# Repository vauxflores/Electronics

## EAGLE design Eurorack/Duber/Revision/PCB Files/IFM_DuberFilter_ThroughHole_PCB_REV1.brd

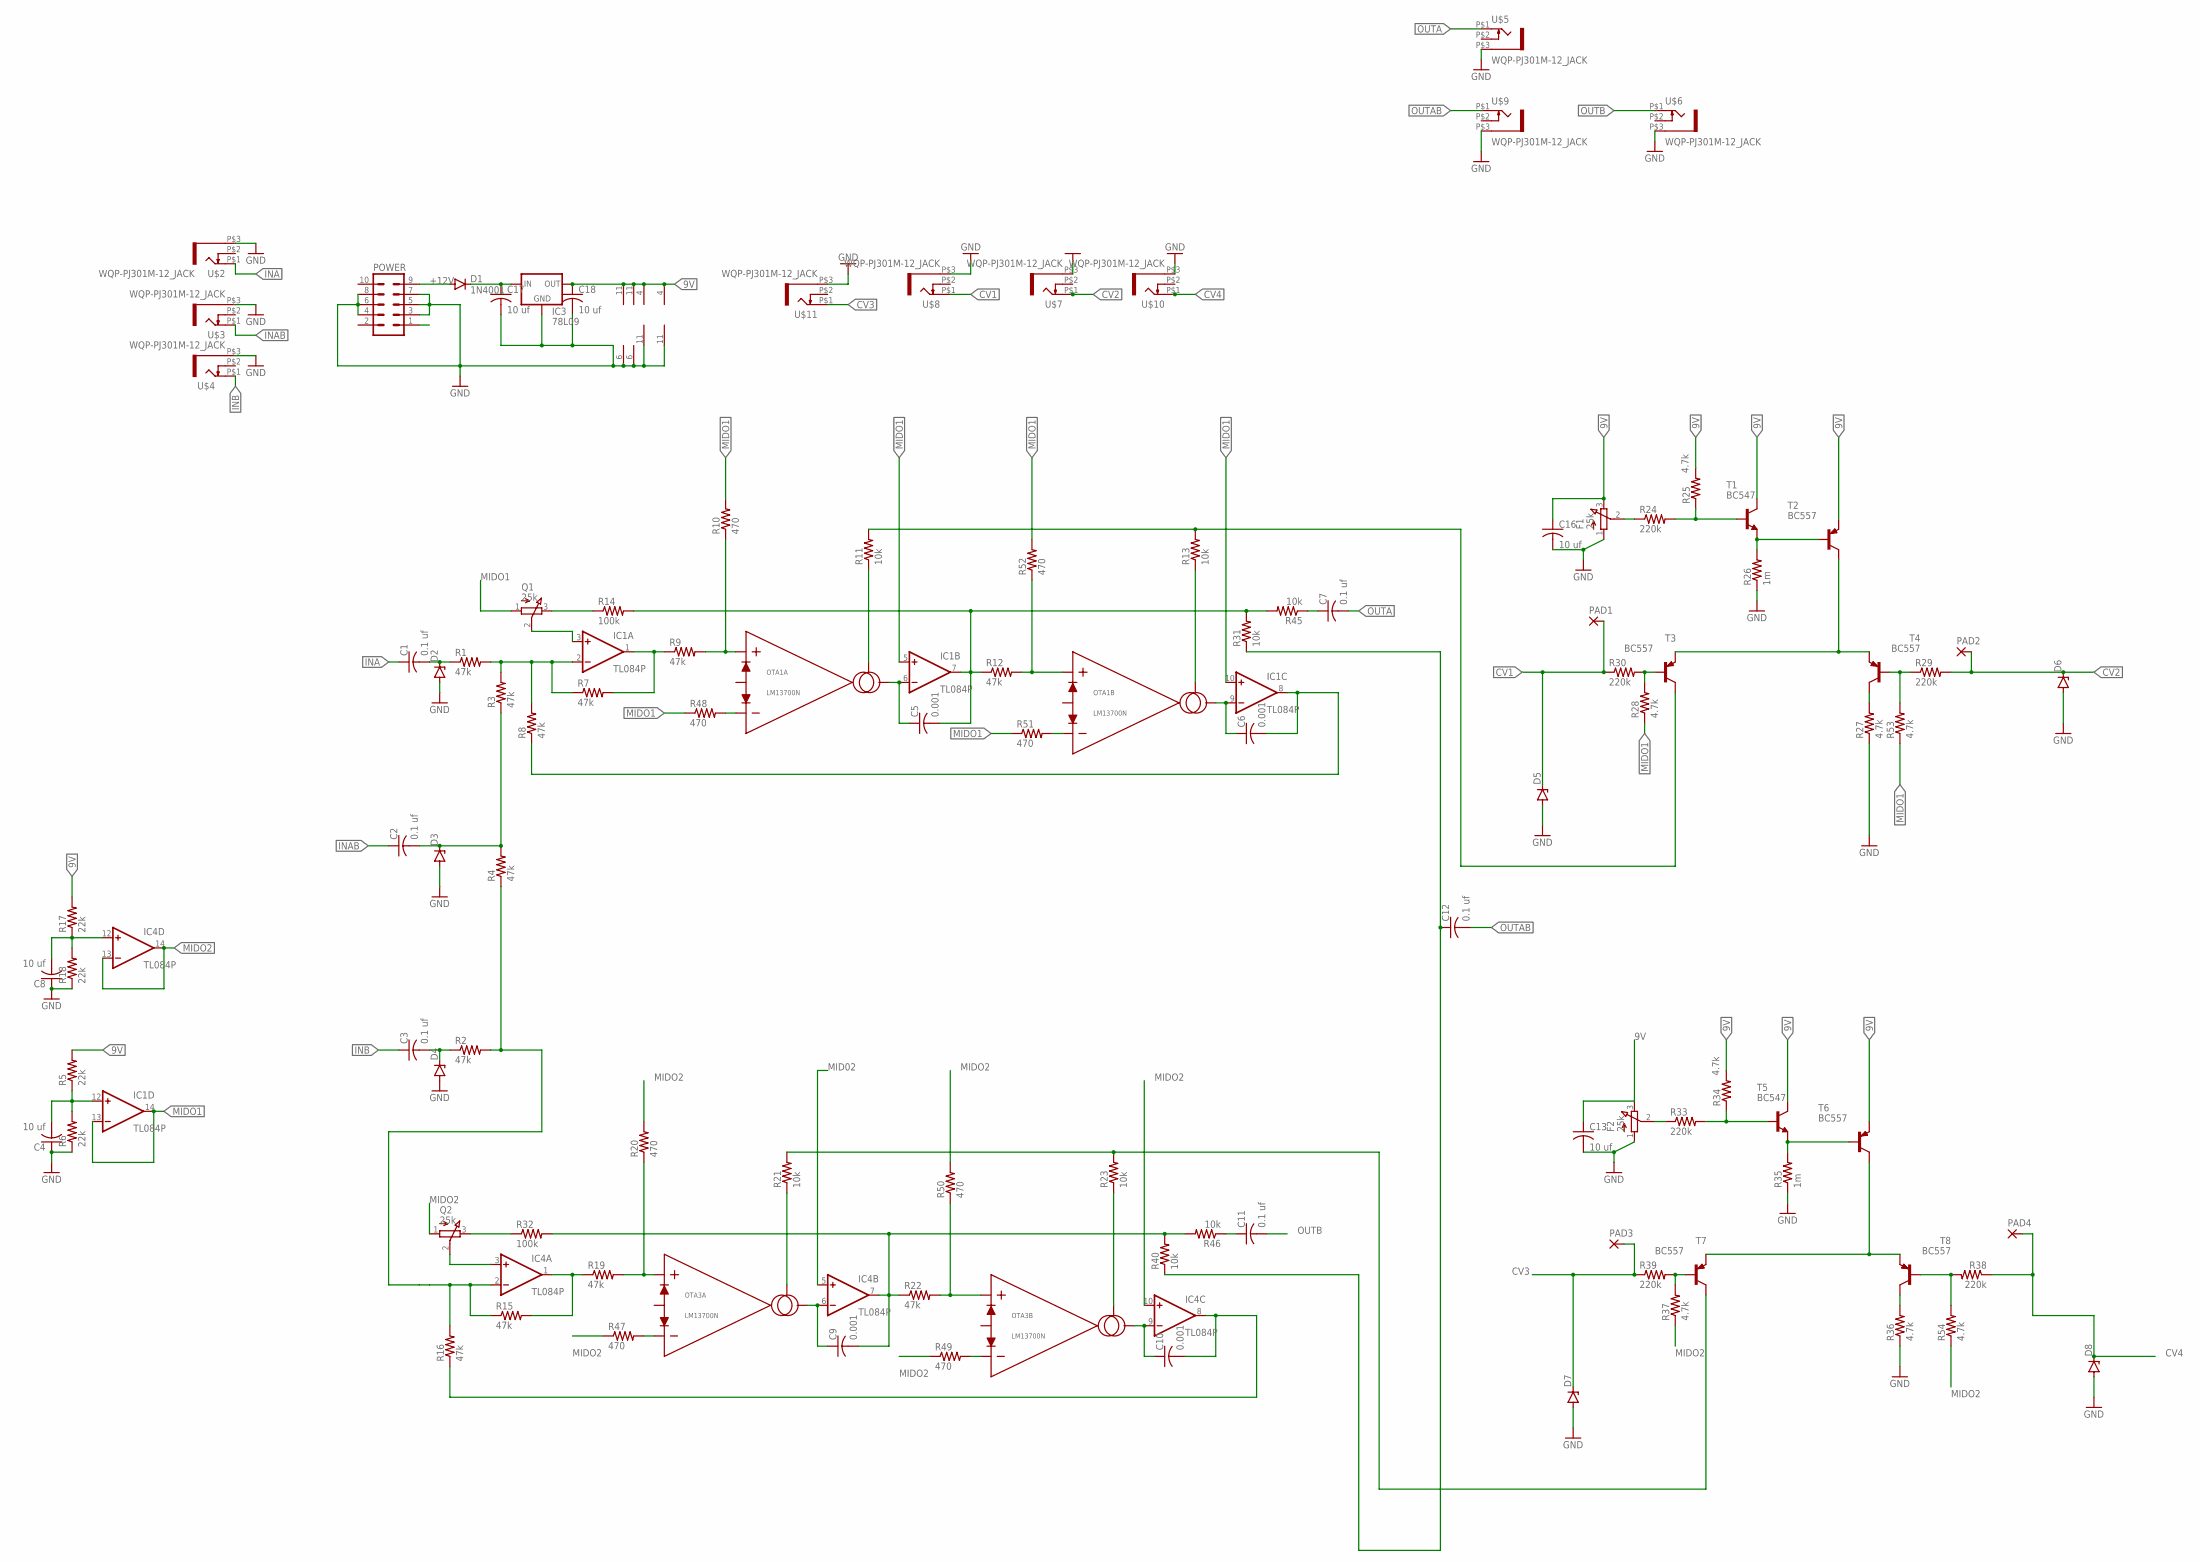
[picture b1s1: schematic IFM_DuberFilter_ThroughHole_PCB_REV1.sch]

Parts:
C1, C2, C3, C7, C11, C12: 0.1 uf; C050-030X075
C4, C8, C13, C16, C17, C18: 10 uf; C050-030X075
C5, C6, C9, C10: 0.001; C050-030X075
D1: 1N4001; DO41-10
D2, D3, D4, D5, D6, D7, D8: ZENER-DIODEDO34-7; DO34Z7
F1, F2: 25k; EVUFXL
IC1, IC4: TL084P; DIL14
IC3: 78L09; 78LXX
OTA1, OTA3: LM13700N; DIP16
PAD1, PAD2, PAD3, PAD4: SMD2; SMD1,27-2,54
POWER: 10_PIN_HEADER; MA05-2
Q1, Q2: 25k; EVUFXL
R1, R2, R3, R4, R7, R8, R9, R12, R15, R16, R19, R22: 47k; 0204/7
R5, R6, R17, R18: 22k; 0204/7
R10, R20, R47, R48, R49, R50, R51, R52: 470; 0204/7
R11, R13, R21, R23, R31, R40, R45, R46: 10k; 0204/7
R14, R32: 100k; 0204/7
R24, R29, R30, R33, R38, R39: 220k; 0204/7
R25, R27, R28, R34, R36, R37, R53, R54: 4.7k; 0204/7
R26, R35: 1m; 0204/7
T1, T5: BC547; TO92
T2, T3, T4, T6, T7, T8: BC557; TO92-EBC
U$2, U$3, U$4, U$5, U$6, U$7, U$8, U$9, U$10, U$11: WQP-PJ301M-12_JACK

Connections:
9V: C13.1, C16.1, C18.1, F1.3 (E), F2.3 (E), IC1.4 (V+), IC3.OUT, IC4.4 (V+), OTA1.11 (VCC), OTA3.11 (VCC), R5.2, R17.2, R25.2, R34.2, T1.3 (C), T2.E, T5.3 (C), T6.E
+12V: C17.1, D1.C, IC3.IN
-12V: POWER.1
CV1: D5.C, PAD1.1, R30.1, U$8.P$1 (2)
CV2: D6.C, PAD2.1, R29.2, U$7.P$1 (2)
CV3: D7.C, PAD3.1, R39.1, U$11.P$1 (2)
CV4: D8.C, PAD4.1, R38.1, U$10.P$1 (2)
GND: C4.1, C8.1, C13.2, C16.2, C17.2, C18.2, D2.A, D3.A, D4.A, D5.A, D6.A, D7.A, D8.A, F1.1 (A), F2.1 (A), IC1.11 (V-), IC3.GND, IC4.11 (V-), OTA1.6 (VEE), OTA3.6 (VEE), POWER.3, POWER.4, POWER.5, POWER.6, POWER.7, POWER.8, R6.1, R18.1, R26.1, R27.1, R35.1, R36.1, U$2.P$3 (1), U$3.P$3 (1), U$4.P$3 (1), U$5.P$3 (1), U$6.P$3 (1), U$7.P$3 (1), U$8.P$3 (1), U$9.P$3 (1), U$10.P$3 (1), U$11.P$3 (1)
INA: C1.1, U$2.P$1 (2)
INAB: C2.1, U$3.P$1 (2)
INB: C3.1, U$4.P$1 (2)
MID02: IC4.5 (+IN)
MIDO1: IC1.5 (+IN), IC1.10 (+IN), IC1.13 (-IN), IC1.14 (OUT), Q1.1 (A), R10.2, R28.1, R48.1, R51.1, R52.2, R53.1
MIDO2: IC4.10 (+IN), IC4.13 (-IN), IC4.14 (OUT), Q2.1 (A), R20.2, R37.1, R47.1, R49.1, R50.2, R54.1
unnamed: C3.2, D4.C, R2.1
unnamed: C1.2, D2.C, R1.1
unnamed: C2.2, D3.C, R3.1, R4.2
unnamed: IC4.2 (-IN), R2.2, R4.1, R15.1, R16.2
unnamed: IC1.2 (-IN), R1.2, R3.2, R7.1, R8.2
unnamed: OTA1.16 (IABC), R13.1
unnamed: C4.2, IC1.12 (+IN), R5.1, R6.2
unnamed: Q1.3 (E), R14.1
unnamed: OTA1.13 (IN-), R51.2
unnamed: IC4.1 (OUT), R15.2, R19.1
unnamed: IC1.1 (OUT), R7.2, R9.1
unnamed: OTA1.3 (IN+), R9.2, R10.1
unnamed: C5.1, IC1.6 (-IN), OTA1.5 (IOUT)
unnamed: OTA1.1 (IABC), R11.1
unnamed: C5.2, IC1.7 (OUT), R12.1, R14.2, R31.2, R45.2
unnamed: R29.1, R53.2, T4.B
unnamed: R11.2, R13.2, T3.C
unnamed: C6.1, IC1.9 (-IN), OTA1.12 (IOUT)
unnamed: C6.2, IC1.8 (OUT), R8.1
unnamed: IC1.3 (+IN), Q1.2 (S)
unnamed: F1.2 (S), R24.1
unnamed: OTA1.14 (IN+), R12.2, R52.1
unnamed: OTA3.3 (IN+), R19.2, R20.1
unnamed: C8.2, IC4.12 (+IN), R17.1, R18.2
unnamed: C9.1, IC4.6 (-IN), OTA3.5 (IOUT)
unnamed: OTA3.1 (IABC), R21.1
unnamed: C9.2, IC4.7 (OUT), R22.1, R32.2, R40.2, R46.2
unnamed: OTA3.16 (IABC), R23.1
unnamed: R21.2, R23.2, T7.C
unnamed: Q2.3 (E), R32.1
unnamed: C10.1, IC4.9 (-IN), OTA3.12 (IOUT)
unnamed: C10.2, IC4.8 (OUT), R16.1
unnamed: D1.A, POWER.9
unnamed: IC4.3 (+IN), Q2.2 (S)
unnamed: OTA1.4 (IN-), R48.2
unnamed: R33.2, R34.1, T5.2 (B)
unnamed: F2.2 (S), R33.1
unnamed: R24.2, R25.1, T1.2 (B)
unnamed: R26.2, T1.1 (E), T2.B
unnamed: T2.C, T3.E, T4.E
unnamed: R35.2, T5.1 (E), T6.B
unnamed: R27.2, T4.C
unnamed: C12.1, R31.1, R40.1
unnamed: R28.2, R30.2, T3.B
unnamed: C11.1, R46.1
unnamed: T6.C, T7.E, T8.E
unnamed: R36.2, T8.C
unnamed: R38.2, R54.2, T8.B
unnamed: R37.2, R39.2, T7.B
unnamed: OTA3.4 (IN-), R47.2
unnamed: OTA3.13 (IN-), R49.2
unnamed: OTA3.14 (IN+), R22.2, R50.1
unnamed: C7.1, R45.1
OUTA: C7.2, U$5.P$1 (2)
OUTAB: C12.2, U$9.P$1 (2)
OUTB: C11.2, U$6.P$1 (2)

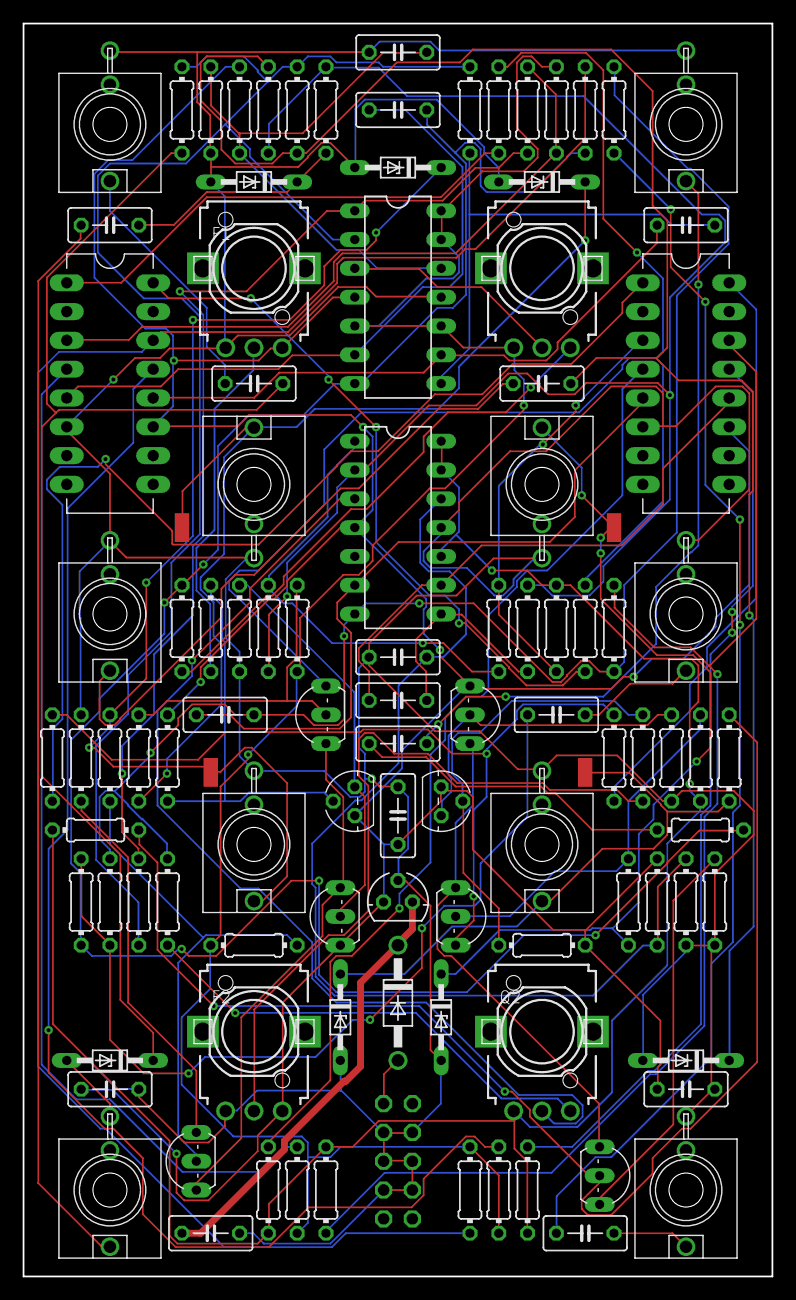
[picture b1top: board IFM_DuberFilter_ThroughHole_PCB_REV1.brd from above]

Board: 2 copper layers, 66.0 x 110.5 mm, 106 parts (1 on the bottom side), 68 nets.

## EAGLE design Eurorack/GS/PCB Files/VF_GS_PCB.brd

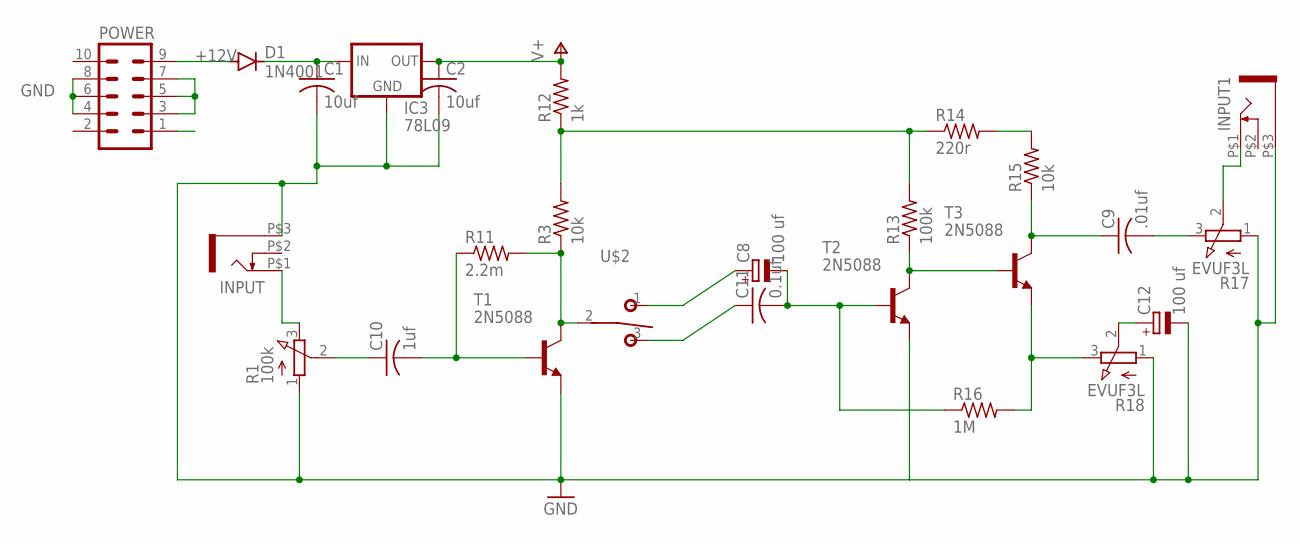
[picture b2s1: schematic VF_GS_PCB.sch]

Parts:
C1, C2: 10uf; C050-025X075
C8, C12: 100 uf; E2,5-6
C9: .01uf; C050-025X075
C10: 1uf; C050-025X075
C11: 0.1uf; C050-025X075
D1: 1N4001; DO41-10
IC3: 78L09; 78LXX
INPUT, INPUT1: WQP-PJ301M-12_JACK
POWER: 10_PIN_HEADER; MA05-2
R1: 100k; EVUFXL
R3, R15: 10k; 0207/7
R11: 2.2m; 0207/7
R12: 1k; 0207/7
R13: 100k; 0207/7
R14: 220r; 0207/7
R16: 1M; 0207/7
R17, R18: EVUF3L; EVUFXL
T1, T2, T3: 2N5088; TO92
U$2: T-80-T-SPDT-ON-OFF-ON; M9040P

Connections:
+12V: C1.1, D1.C, IC3.IN
-12V: POWER.1
GND: C1.2, C2.2, C12.-, IC3.GND, INPUT.P$3 (1), INPUT1.P$3 (1), POWER.3, POWER.4, POWER.5, POWER.6, POWER.7, POWER.8, R1.1 (A), R17.1 (A), R18.1 (A), T1.3 (E), T2.3 (E)
unnamed: C10.1, R1.2 (S)
unnamed: INPUT.P$1 (2), R1.3 (E)
unnamed: INPUT1.P$1 (2), R17.2 (S)
unnamed: D1.A, POWER.9
unnamed: C10.2, R11.1, T1.2 (B)
unnamed: R3.1, R11.2, T1.1 (C), U$2.2
unnamed: R3.2, R12.1, R13.2, R14.1
unnamed: C8.-, C11.2, R16.1, T2.2 (B)
unnamed: R13.1, T2.1 (C), T3.2 (B)
unnamed: R14.2, R15.2
unnamed: C9.1, R15.1, T3.1 (C)
unnamed: C9.2, R17.3 (E)
unnamed: C12.+, R18.2 (S)
unnamed: C11.1, U$2.3 (S)
unnamed: C8.+, U$2.1 (O)
unnamed: R16.2, R18.3 (E), T3.3 (E)
V+: C2.1, IC3.OUT, R12.2

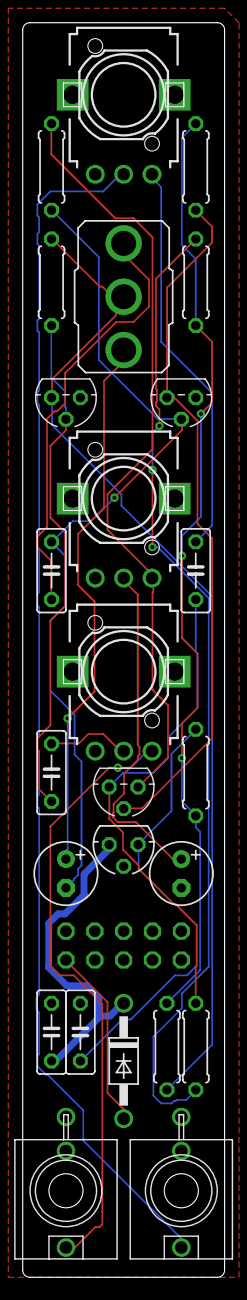
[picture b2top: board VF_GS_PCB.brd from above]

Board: 2 copper layers, 17.8 x 110.5 mm, 27 parts (1 on the bottom side), 19 nets.

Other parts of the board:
U$1: EURO_PCB_4HP

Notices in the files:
parts and their libraries:
OTAs: Copyright © David H. Christensen, 2017.
